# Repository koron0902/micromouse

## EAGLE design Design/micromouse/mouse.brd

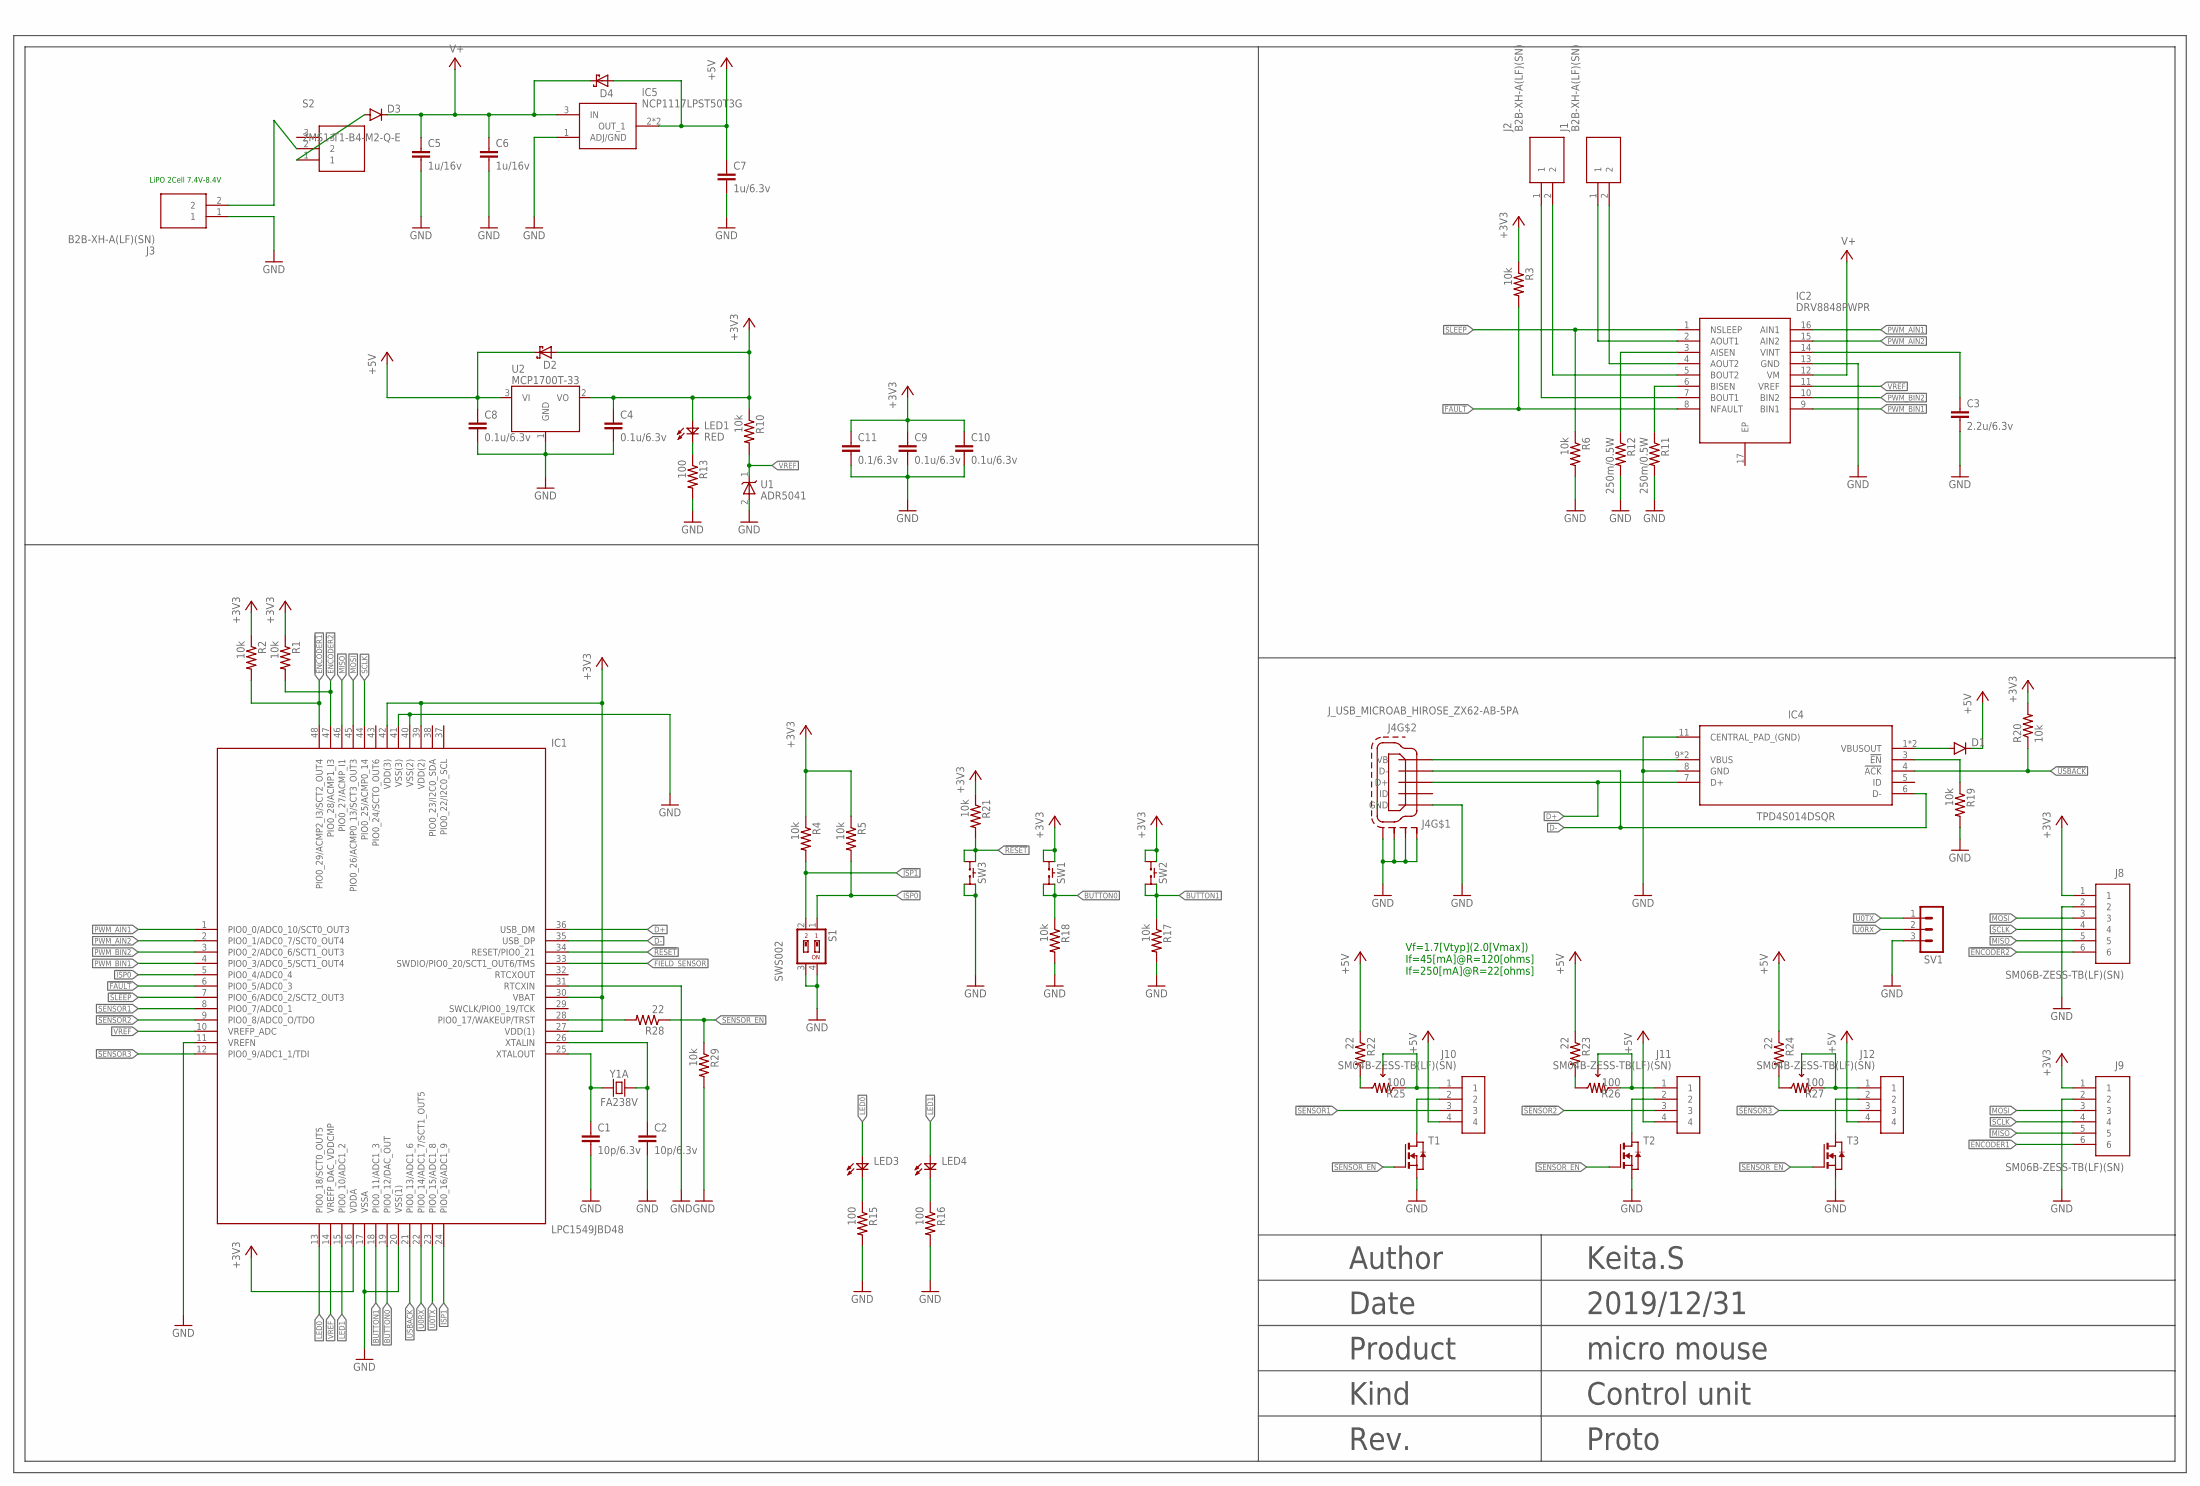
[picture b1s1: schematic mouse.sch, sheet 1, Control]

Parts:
C1, C2: 10p/6.3v; C0603
C3: 2.2u/6.3v; C0603
C4, C8, C9, C10: 0.1u/6.3v; C0603
C5, C6: 1u/16v; C0603
C7: 1u/6.3v; C0603
C11: 0.1/6.3v; C0603
D1, D3: DIODE-SMB; SMB
D2, D4: SBD-SOD523; DIODE_SOD523
IC1: LPC1549JBD48; QFP50P900X900X160-48N
IC2: DRV8848PWPR; SOP65P640X120-17N
IC4: TPD4S014DSQR; SON40P200X200X80-11N
IC5: NCP1117LPST50T3G; SOT230P700X180-4N
J1, J2, J3: B2B-XH-A(LF)(SN); SHDR2W64P0X250_1X2_740X575X700
J4: J_USB_MICROAB_HIROSE_ZX62-AB-5PA
J8, J9: SM06B-ZESS-TB(LF)(SN); SM06BZESSTBLFSN
J10, J11, J12: SM04B-ZESS-TB(LF)(SN); SM04BZESSTBLFSN
LED1: RED; LED1608
LED3, LED4: LED1608
R1, R2, R3, R4, R5, R6, R10, R17, R18, R19, R20, R21, R29: 10k; R0603
R11, R12: 250m/0.5W; R1206
R13, R15, R16: 100; R0603
R22, R23, R24, R28: 22; R0603
R25, R26, R27: 100; CT6EP203
S1: SWS002; SMS-002
S2: 2MS1-T1-B4-M2-Q-E
SV1: MA03-1
SW1, SW2, SW3: SKRP
T1, T2, T3: NMOSSOT23; SOT-23
U1: ADR5041; SC70-3
U2: MCP1700T-33; SOT23-3
Y1: FA238V; EPSON_FA238V

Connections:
!ENCODER1: IC1.48 (PIO0_29/ACMP2_I3/SCT2_OUT4), J9.6, R2.2
!ENCODER2: IC1.47 (PIO0_28/ACMP1_I3), J8.6, R1.2
!FAULT: IC1.6 (PIO0_5/ADC0_3), IC2.8 (NFAULT), R3.2
!ISP0: IC1.5 (PIO0_4/ADC0_4), R5.2, S1.1
!ISP1: IC1.24 (PIO0_16/ADC1_9), R4.2, S1.2
!RESET: IC1.34 (RESET/PIO0_21), R21.2, SW3.A1, SW3.A2
!SENSOR1: IC1.8 (PIO0_7/ADC0_1), J10.3
!SENSOR2: IC1.9 (PIO0_8/ADC0_O/TDO), J11.3
!SENSOR3: IC1.12 (PIO0_9/ADC1_1/TDI), J12.3
!SLEEP: IC1.7 (PIO0_6/ADC0_2/SCT2_OUT3), IC2.1 (NSLEEP), R6.1
!USBACK: IC1.21 (PIO0_13/ADC1_6), IC4.4 (!ACK), R20.1
+3V3: C4.1, C9.1, C10.1, C11.1, D2.A, IC1.16 (VDDA), IC1.27 (VDD(1)), IC1.30 (VBAT), IC1.39 (VDD(2)), IC1.42 (VDD(3)), J8.1, J9.1, LED1.A, R1.1, R2.1, R3.1, R4.1, R5.1, R10.1, R20.2, R21.1, SW1.A1, SW1.A2, SW2.A1, SW2.A2, U2.2 (VO)
+5V: C7.1, C8.1, D1.C, D2.K, D4.A, IC5.2 (OUT_1), IC5.4 (OUT_1), J10.4, J11.4, J12.4, R22.1, R23.1, R24.1, U2.3 (VI)
BUTTON0: IC1.19 (PIO0_12/DAC_OUT), R18.1, SW1.B1, SW1.B2
BUTTON1: IC1.18 (PIO0_11/ADC1_3), R17.1, SW2.B1, SW2.B2
D+: IC1.36 (USB_DM), IC4.7 (D+), J4.P$3 (D+)
D-: IC1.35 (USB_DP), IC4.6 (D-), J4.P$2 (D-)
FIELD_SENSOR: IC1.33 (SWDIO/PIO0_20/SCT1_OUT6/TMS)
GND: C1.2, C2.2, C3.2, C4.2, C5.2, C6.2, C7.2, C8.2, C9.2, C10.2, C11.2, IC1.11 (VREFN), IC1.17 (VSSA), IC1.20 (VSS(1)), IC1.31 (RTCXIN), IC1.40 (VSS(2)), IC1.41 (VSS(3)), IC2.13 (GND), IC4.8 (GND), IC4.11 (CENTRAL_PAD_(GND)), IC5.1 (ADJ/GND), J3.1, J4.P$5 (GND), J4.SHIELD1 (S1), J4.SHIELD2 (S2), J4.SHIELD3 (S3), J4.SHIELD4 (S4), J8.2, J9.2, R6.2, R11.2, R12.2, R13.2, R15.2, R16.2, R17.2, R18.2, R19.2, R29.2, S1.3, S1.4, SV1.3, SW3.B1, SW3.B2, T1.2 (S), T2.2 (S), T3.2 (S), U1.2 (A), U2.1 (GND)
LED0: IC1.13 (PIO0_18/SCT0_OUT5), LED3.A
LED1: IC1.15 (PIO0_10/ADC1_2), LED4.A
MISO: IC1.46 (PIO0_27/ACMP_I1), J8.5, J9.5
MOSI: IC1.45 (PIO0_26/ACMP0_13/SCT3_OUT3), J8.3, J9.3
unnamed: C1.1, IC1.25 (XTALOUT), Y1.1
unnamed: C2.1, IC1.26 (XTALIN), Y1.3
unnamed: D3.A, S2.1
unnamed: R22.2, R25.1 (CCW)
unnamed: IC2.6 (BISEN), R11.1
unnamed: D1.A, IC4.1 (VBUSOUT), IC4.2 (VBUSOUT)
unnamed: C3.1, IC2.14 (VINT)
unnamed: J3.2, S2.2
unnamed: LED1.K, R13.1
unnamed: IC2.2 (AOUT1), J1.1
unnamed: IC2.4 (AOUT2), J1.2
unnamed: IC2.5 (BOUT2), J2.2
unnamed: IC2.7 (BOUT1), J2.1
unnamed: IC2.3 (AISEN), R12.1
unnamed: LED3.K, R15.1
unnamed: IC4.3 (!EN), R19.1
unnamed: LED4.K, R16.1
unnamed: R23.2, R26.1 (CCW)
unnamed: IC4.9 (VBUS), IC4.10 (VBUS), J4.P$1 (VB)
unnamed: J11.1, R26.2 (WIPER), R26.3 (CW)
unnamed: R24.2, R27.1 (CCW)
unnamed: J12.1, R27.2 (WIPER), R27.3 (CW)
unnamed: IC1.28 (PIO0_17/WAKEUP/TRST), R28.2
unnamed: J10.2, T1.1 (D)
unnamed: J10.1, R25.2 (WIPER), R25.3 (CW)
unnamed: J11.2, T2.1 (D)
unnamed: J12.2, T3.1 (D)
PWM_AIN1: IC1.1 (PIO0_0/ADC0_10/SCT0_OUT3), IC2.16 (AIN1)
PWM_AIN2: IC1.2 (PIO0_1/ADC0_7/SCT0_OUT4), IC2.15 (AIN2)
PWM_BIN1: IC1.4 (PIO0_3/ADC0_5/SCT1_OUT4), IC2.9 (BIN1)
PWM_BIN2: IC1.3 (PIO0_2/ADC0_6/SCT1_OUT3), IC2.10 (BIN2)
SCLK: IC1.44 (PIO0_25/ACMP0_14), J8.4, J9.4
SENSOR_EN: R28.1, R29.1, T1.3 (G), T2.3 (G), T3.3 (G)
U0RX: IC1.22 (PIO0_14/ADC1_7/SCT1_OUT5), SV1.2
U0TX: IC1.23 (PIO0_15/ADC1_8), SV1.1
V+: C5.1, C6.1, D3.C, D4.K, IC2.12 (VM), IC5.3 (IN)
VREF: IC1.10 (VREFP_ADC), IC1.14 (VREFP_DAC_VDDCMP), IC2.11 (VREF), R10.2, U1.1 (K)

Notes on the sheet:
Author
Date
Product
Kind
Rev.
Keita.S
2019/12/31
micro mouse
Control unit
Proto
LiPO 2Cell 7.4V-8.4V
Vf=1.7[Vtyp](2.0[Vmax]) If=45[mA]@R=120[ohms] If=250[mA]@R=22[ohms]

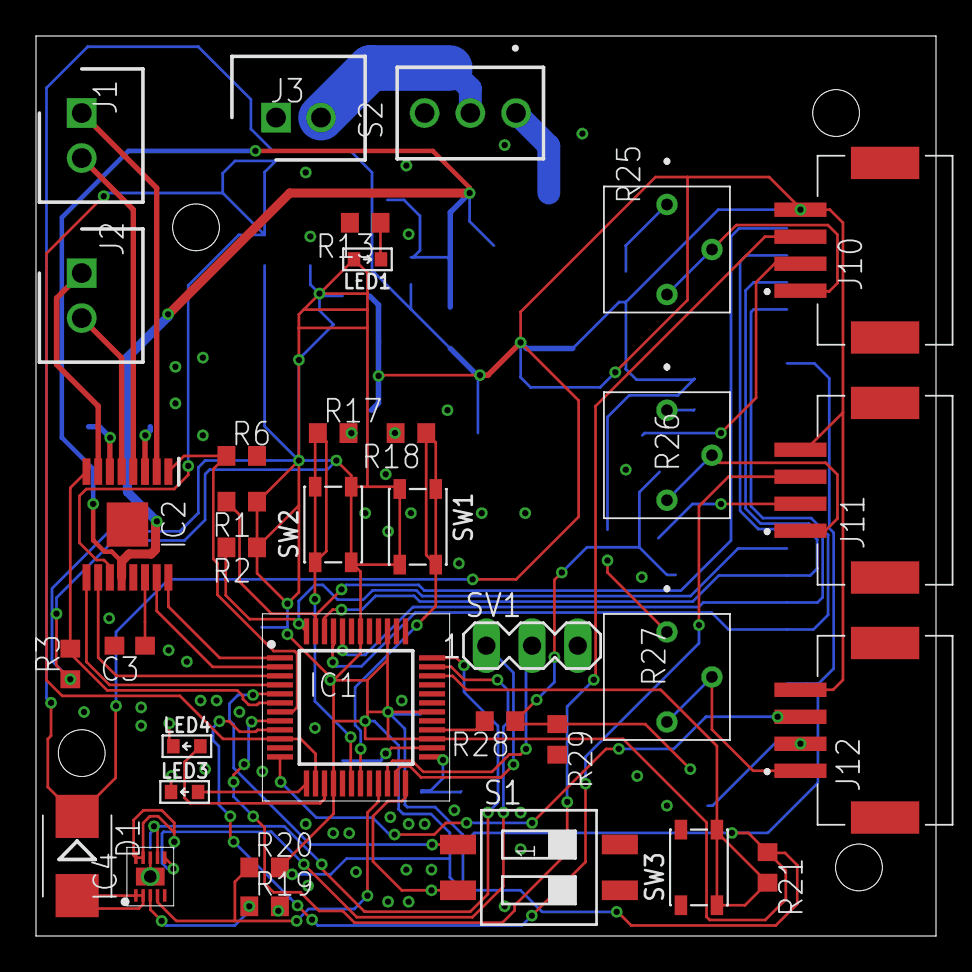
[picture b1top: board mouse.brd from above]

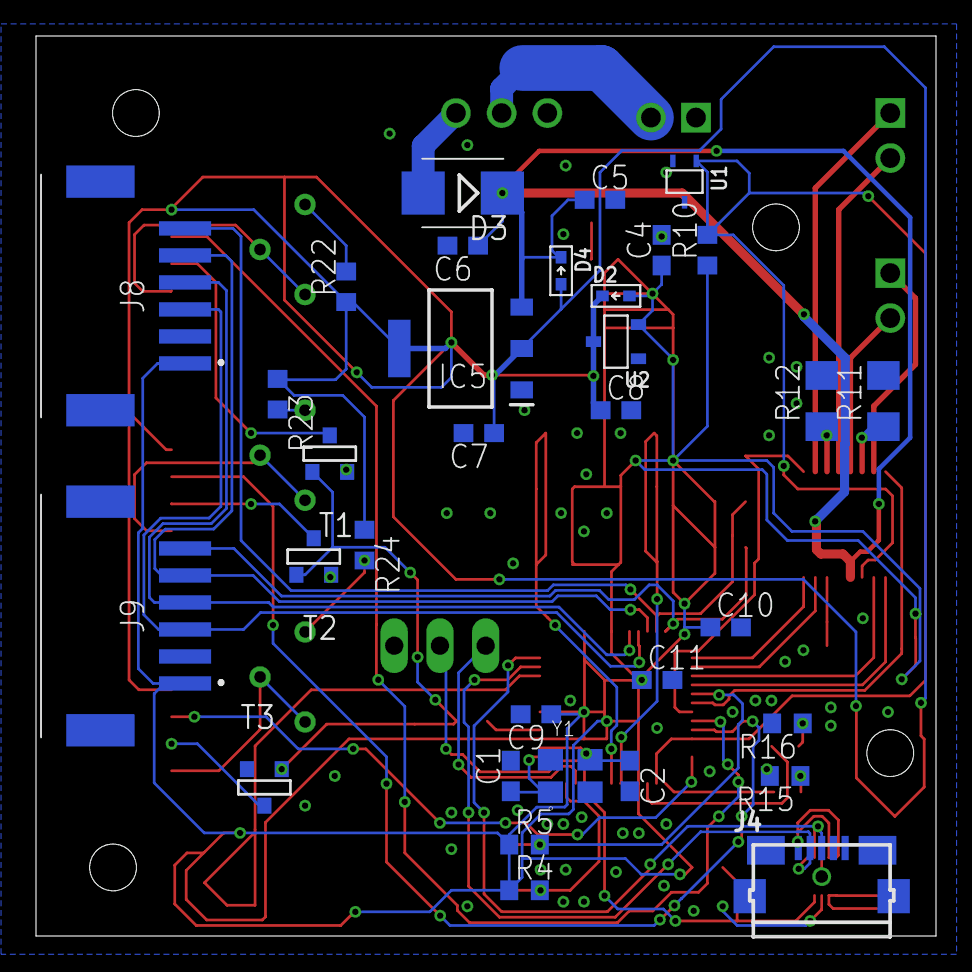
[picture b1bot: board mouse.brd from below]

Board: 2 copper layers, 50.0 x 50.0 mm, 68 parts (33 on the bottom side), 59 nets.

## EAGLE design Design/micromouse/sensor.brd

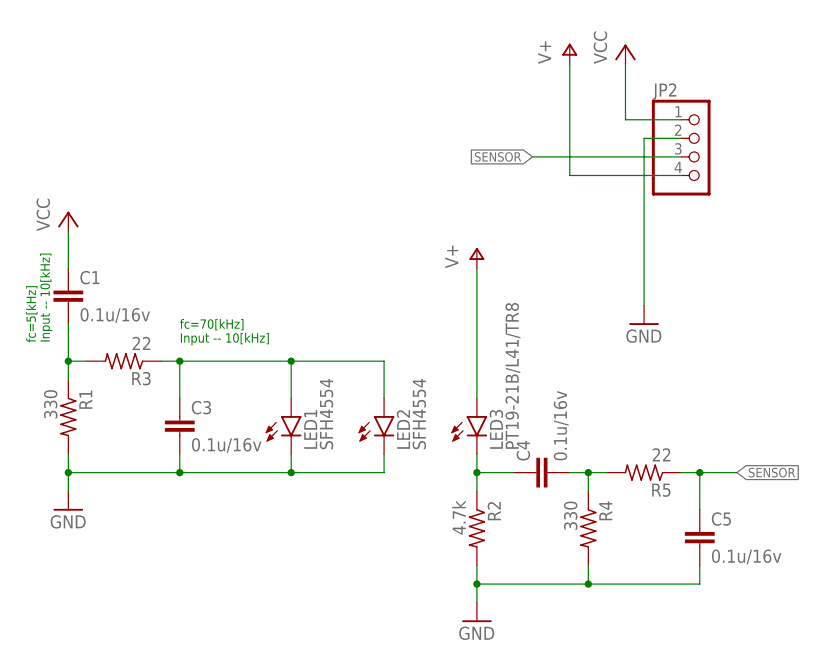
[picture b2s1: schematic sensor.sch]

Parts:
C1, C3, C4, C5: 0.1u/16v; C0603
JP2: PINHD-1X4/90; 1X04/90
LED1, LED2: SFH4554; LED5MM
LED3: PT19-21B/L41/TR8; SML0603
R1, R4: 330; R0603
R2: 4.7k; R0603
R3, R5: 22; R0603

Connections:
GND: C3.2, C5.2, JP2.2, LED1.K (C), LED2.K (C), R1.2, R2.2, R4.2
unnamed: C3.1, LED1.A, LED2.A, R3.1
unnamed: C4.1, LED3.C, R2.1
unnamed: C1.2, R1.1, R3.2
unnamed: C4.2, R4.1, R5.2
SENSOR: C5.1, JP2.3, R5.1
V+: JP2.4, LED3.A
VCC: C1.1, JP2.1

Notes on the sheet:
fc=5[kHz] Input -- 10[kHz]
fc=70[kHz] Input -- 10[kHz]

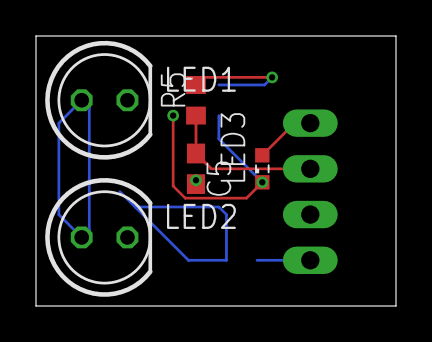
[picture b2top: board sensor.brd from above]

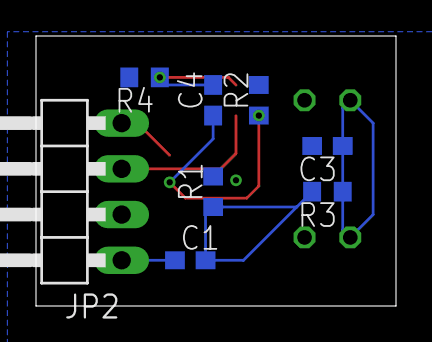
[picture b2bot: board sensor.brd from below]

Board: 2 copper layers, 20.0 x 15.0 mm, 13 parts (8 on the bottom side), 8 nets.

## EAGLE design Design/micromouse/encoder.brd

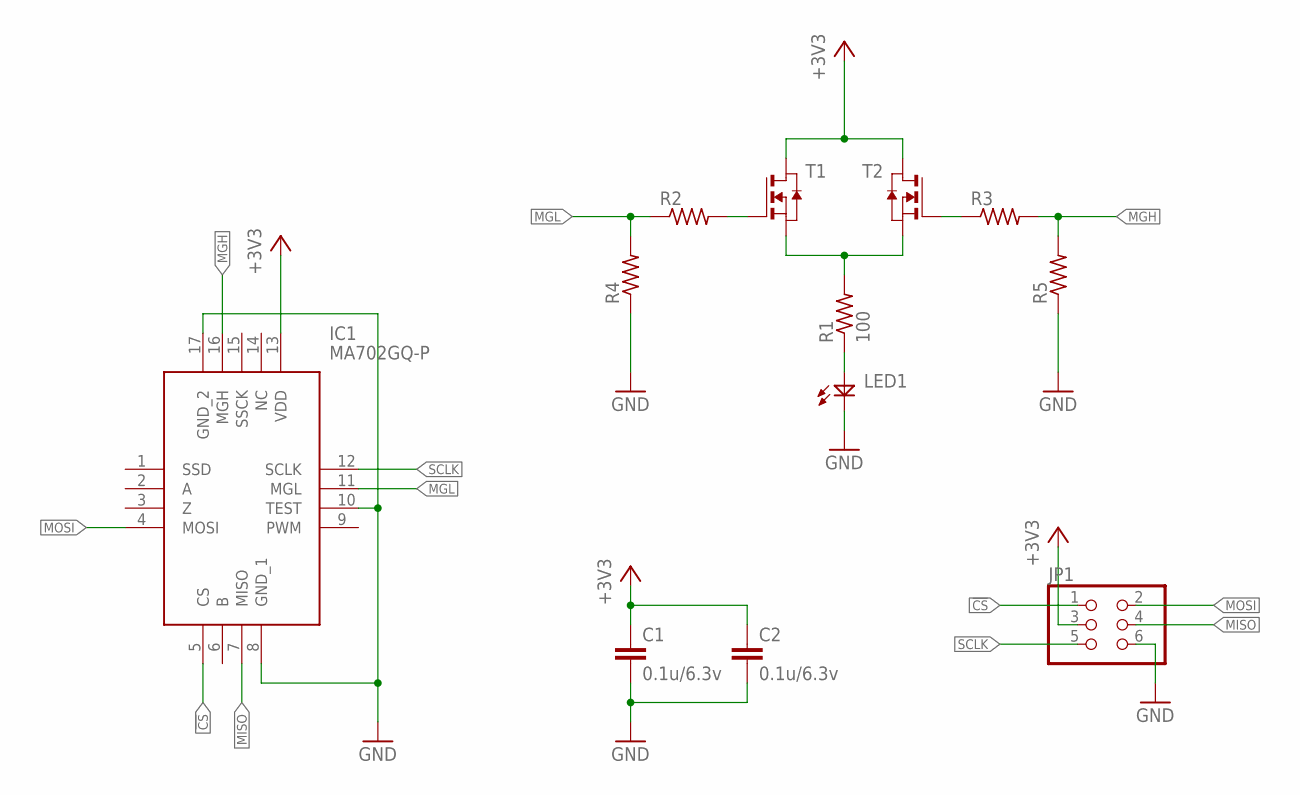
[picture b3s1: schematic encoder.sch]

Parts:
C1, C2: 0.1u/6.3v; C0603
IC1: MA702GQ-P; QFN50P300X300X100-17N
JP1: PINHD-2X3/90; 2X03/90
LED1: LED1608
R1: 100; R0603
R2, R3, R4, R5: R-US_R0603; R0603
T1, T2: NMOSSOT23; SOT-23

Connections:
!CS: IC1.5 (CS), JP1.1
+3V3: C1.1, C2.1, IC1.13 (VDD), JP1.3, T1.1 (D), T2.1 (D)
GND: C1.2, C2.2, IC1.8 (GND_1), IC1.10 (TEST), IC1.17 (GND_2), JP1.6, LED1.K, R4.1, R5.1
MGH: IC1.16 (MGH), R3.2, R5.2
MGL: IC1.11 (MGL), R2.1, R4.2
MISO: IC1.7 (MISO), JP1.4
MOSI: IC1.4 (MOSI), JP1.2
unnamed: LED1.A, R1.1
unnamed: R1.2, T1.2 (S), T2.2 (S)
unnamed: R2.2, T1.3 (G)
unnamed: R3.1, T2.3 (G)
SCLK: IC1.12 (SCLK), JP1.5

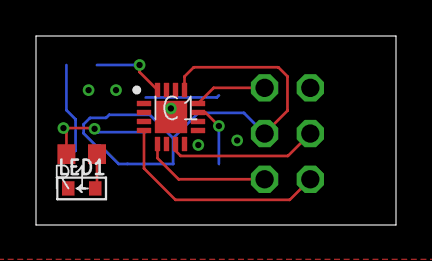
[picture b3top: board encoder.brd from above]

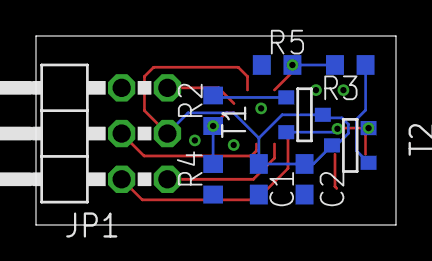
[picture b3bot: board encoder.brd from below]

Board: 2 copper layers, 20.0 x 10.5 mm, 12 parts (9 on the bottom side), 12 nets.

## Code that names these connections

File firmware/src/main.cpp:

/*
===============================================================================
 Name        : main.c
 Author      : $(author)
 Version     :
 Copyright   : $(copyright)
 Description : main definition
===============================================================================
*/
#include <cr_section_macros.h>

#include <array>

#include "driver/AnalogIn.hpp"
#include "driver/DigitalIO.hpp"
#include "driver/comm/SPI.hpp"
#include "driver/PWM.hpp"
#include "driver/comm/usb.hpp"
#include "driver/systick.hpp"

const uint32_t OscRateIn = 12000000;
const uint32_t RTCOscRateIn = 32768;

int main(void) {

	Driver::Tick::Init();


	/******* GPIO Definitions *******/
	Driver::GPIO::Digital Button0(0, 12);
	Driver::GPIO::Digital Button1(0, 11);
	Driver::GPIO::Digital LED0(0, 18);
	Driver::GPIO::Digital LED1(0, 10);
	Driver::GPIO::Digital nFault(0, 5);
	Driver::GPIO::Digital nSleep(0, 6);


	/******* PWM Definitions *******/
	Driver::PWM Ain1({0, 0}, Driver::PWM::PWMCh::Ch3);
	Driver::PWM Ain2({0, 0}, Driver::PWM::PWMCh::Ch4);
	Driver::PWM Bin1({0, 0}, Driver::PWM::PWMCh::Ch11);
	Driver::PWM Bin2({0, 0}, Driver::PWM::PWMCh::Ch12);
	Driver::PWM SensorEn({0, 17}, Driver::PWM::PWMCh::Ch0);


	Driver::SPI encoder(1, {0, 26}, {0, 27}, {0, 25});
	encoder.SetCS({0, 29}, 0, 0);
	encoder.SetCS({0, 28}, 1, 0);

	encoder.SetBitWidth(16);
	encoder.SetFreq(4000000);

	Driver::USB usb;

	std::array<Driver::GPIO::Analog, 3> Sensor{
		Driver::GPIO::Analog(0, 7, 0, 1),
		Driver::GPIO::Analog(0, 8, 0, 0),
		Driver::GPIO::Analog(0, 9, 1, 1)
	};


    // TODO: insert code here

    // Force the counter to be placed into memory
    volatile static int i = 0 ;
    // Enter an infinite loop, just incrementing a counter
    while(1) {
        i++ ;
    }
    return 0 ;
}

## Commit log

2020-01-06 add firmware
2020-01-07 trace makefiles with git
2020-01-07 modify mk files
2020-01-07 create Jenkinsfile
2020-01-07 refuctoring
2020-01-07 ModifyMakeFile.py
2020-01-07 wercker
2020-01-07 modify cproj
2020-01-07 modify MODIFIER
2020-01-07 circuit design
2020-01-19 submodule
